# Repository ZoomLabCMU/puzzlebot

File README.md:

# PuzzleBots: Physical Coupling of Robot Swarms
Sha Yi, Zeynep Temel, Katia Sycara

Link to our [video](https://www.youtube.com/watch?v=QP3eMZXLSw4). We present a guide to make and run our PuzzleBots. A newer version is available [here](https://github.com/ZoomLabCMU/puzzlebot_v2).  

If you find our work useful, please consider citing our paper:  
```
@inproceedings{yi2021puzzlebots,
  title={PuzzleBots: Physical Coupling of Robot Swarms},
  author={Yi, Sha and Temel, Zeynep and Sycara, Katia},
  booktitle={2021 IEEE International Conference on Robotics and Automation (ICRA)},
  pages={8742--8748},
  year={2021},
  organization={IEEE}
}
```

**Software Requirement**
- python
- ROS
- Arduino

**Hardware Requirement**
- 3D Printer
- Soldering Iron
- Circuit Board Production (may use external manufacturer)
- Vicon (or other localization systems)

## Preparation
1. Assemble the robot based on instructions from the [assembly page](docs/assembly.md).
2. Burn bootloader of Arduino Pro Mini (8M, 3.3V) to the ATMega328P.
3. Configure ESP8266 WiFi module with baud rate to be 9600.

## Run the Demo
### Setup
1. Configure the system  
Change Line 83 and 105 in `code/puzzlebot_arduino/wifitcp_motor_only/wifitcp_motor_only.ino` to your own wifi and IP address.
2. Load program onto circuit board  
Open the program `code/puzzlebot_arduino/wifitcp_motor_only/wifitcp_motor_only.ino` in Arduino Studio (or other Software) and load to the circuit board built in [assembly page](docs/assembly.md).
3. Build ROS package  
Copy `code/puzzlebot_control/` into the ROS catkin source directory. Build the package.

### Run
Each robot is associated with an IP address. In our setting, robot IP address has the form `192.168.0.20[ROBOT_ID]`. The corresponding Vicon ROS topic thus has the form `vicon/p20[ROBOT_ID]/p20[ROBOT_ID]`. For example, robot #2 has an IP of `192.168.0.202`, and the corresponding vicon topic is `vicon/p202/p202`.  
This can be changed in `code/puzzlebot_control/src/puzzlebot_control/hardware_wrap.py` Line 33. To turn off the vicon callback, change Line 30 in the `hardware_wrap.py` file.

Before launching the puzzlebot node, make sure the Vicon (or other localization system) is running and publishing the corret ROS topics. Then do
```
rosrun puzzlebot_control run_hardware.py [NUMBER_OF_ROBOTS]
```
For example, with three robots, run `rosrun puzzlebot_control run_hardware.py 3`.

Then, switch on the robots by sliding the switch on the top. You are expected to see the ESP8266 LED flashes then the console will show robots are connected in sequence. The program will start once all robots are connected.

### Testing Functions
A testing function `keyboard_input_lr` is provided in `robot.py`. It can be called in `hardware_wrap.py` to send velocity command during runtime to the robots to help debug hardware issues.

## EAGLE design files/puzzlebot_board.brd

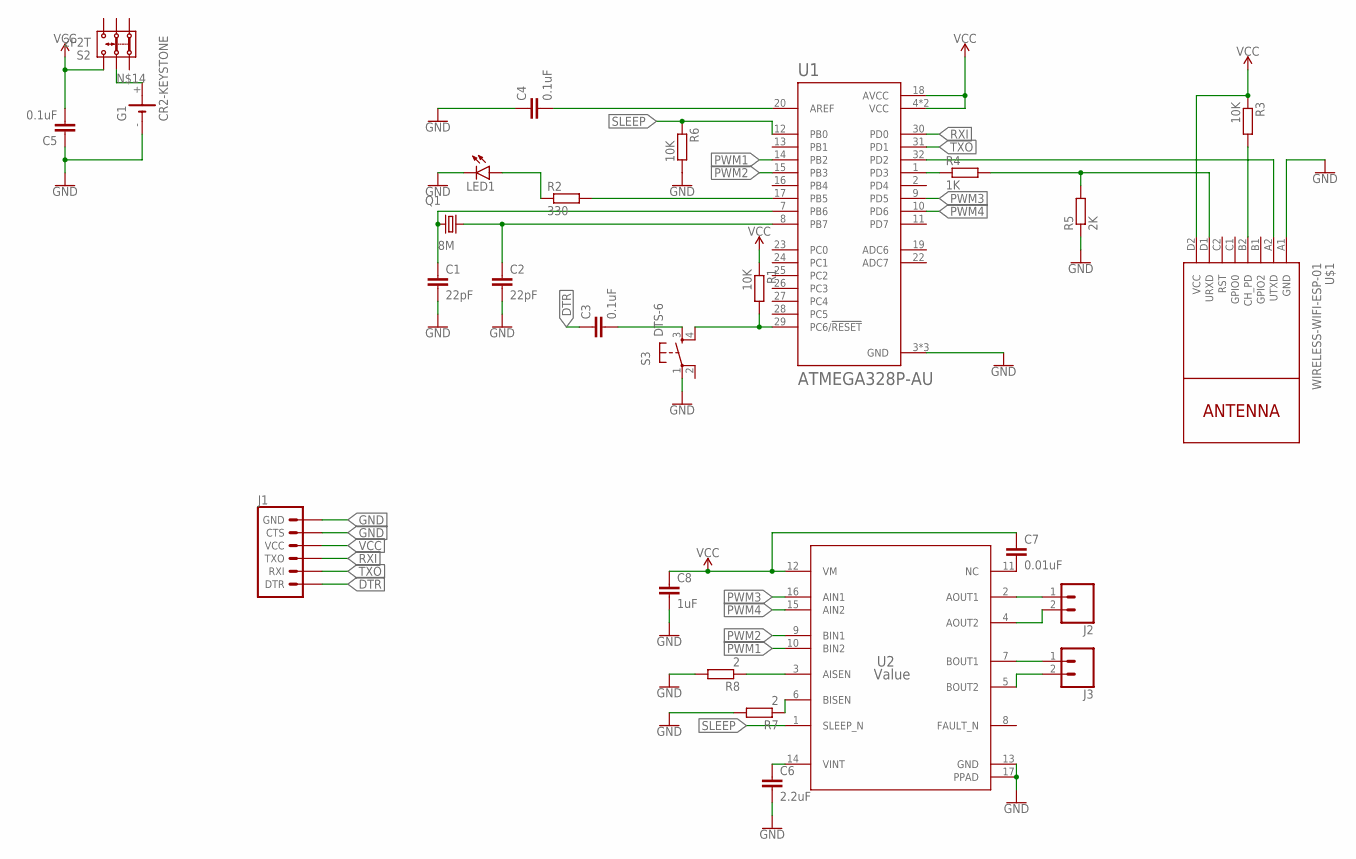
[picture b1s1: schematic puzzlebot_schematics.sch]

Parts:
C1, C2: 22pF; C0603
C3, C4, C5: 0.1uF; C0603
C6: 2.2uF; C0603
C7: 0.01uF; C0603
C8: 1uF; C0603
G1: CR2-KEYSTONE; SL-150-1/2AA/PR
J1: 6_PIN_SERIAL_TARGETLONGPADS; 1X06_LONGPADS
J2, J3: CONN_02POLAR; MOLEX-1X2
LED1: LEDCHIP-LED0805; CHIP-LED0805
Q1: 8M; CSM-7X-DU
R1, R3, R6: 10K; R0603
R2: 330; R0603
R4: 1K; R0603
R5: 2K; R0603
R7, R8: 2; R0603
S2: 2P2T
S3: DTS-6
U1: ATMEGA328P-AU; QFP80P900X900X120-32N
U2: Value; PWP0016K_M
U$1: WIRELESS-WIFI-ESP-01

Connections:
DTR: C3.1, J1.1 (DTR)
GND: C1.2, C2.2, C4.1, C5.1, C6.2, C8.2, G1.-, J1.5 (CTS), J1.6 (GND), LED1.C, R5.1, R6.2, R7.2, R8.2, S3.1, U1.3 (GND), U1.5 (GND), U1.21 (GND), U2.13 (GND), U2.17 (PPAD), U$1.A1 (GND)
unnamed: C2.1, Q1.2, U1.8 (PB7)
unnamed: C1.1, Q1.1, U1.7 (PB6)
unnamed: C3.2, S3.3
unnamed: R1.2, S3.4, U1.29 (PC6/!RESET)
unnamed: R3.2, U$1.B2 (CH_PD)
unnamed: R2.2, U1.17 (PB5)
unnamed: LED1.A, R2.1
unnamed: C4.2, U1.20 (AREF)
unnamed: U1.32 (PD2), U$1.A2 (UTXD)
unnamed: R4.1, U1.1 (PD3)
unnamed: R4.2, R5.2, U$1.D1 (URXD)
unnamed: C6.1, U2.14 (VINT)
unnamed: C7.2, U2.11 (NC)
unnamed: G1.+, S2.2.1
unnamed: R7.1, U2.6 (BISEN)
unnamed: R8.1, U2.3 (AISEN)
unnamed: J2.1, U2.2 (AOUT1)
unnamed: J3.1, U2.7 (BOUT1)
unnamed: J2.2, U2.4 (AOUT2)
unnamed: J3.2, U2.5 (BOUT2)
PWM1: U1.14 (PB2), U2.10 (BIN2)
PWM2: U1.15 (PB3), U2.9 (BIN1)
PWM3: U1.9 (PD5), U2.16 (AIN1)
PWM4: U1.10 (PD6), U2.15 (AIN2)
RXI: J1.3 (TXO), U1.30 (PD0)
SLEEP: R6.1, U1.12 (PB0), U2.1 (SLEEP_N)
TXO: J1.2 (RXI), U1.31 (PD1)
VCC: C5.2, C7.1, C8.1, J1.4 (VCC), R1.1, R3.1, S2.3.1, U1.4 (VCC), U1.6 (VCC), U1.18 (AVCC), U2.12 (VM), U$1.D2 (VCC)

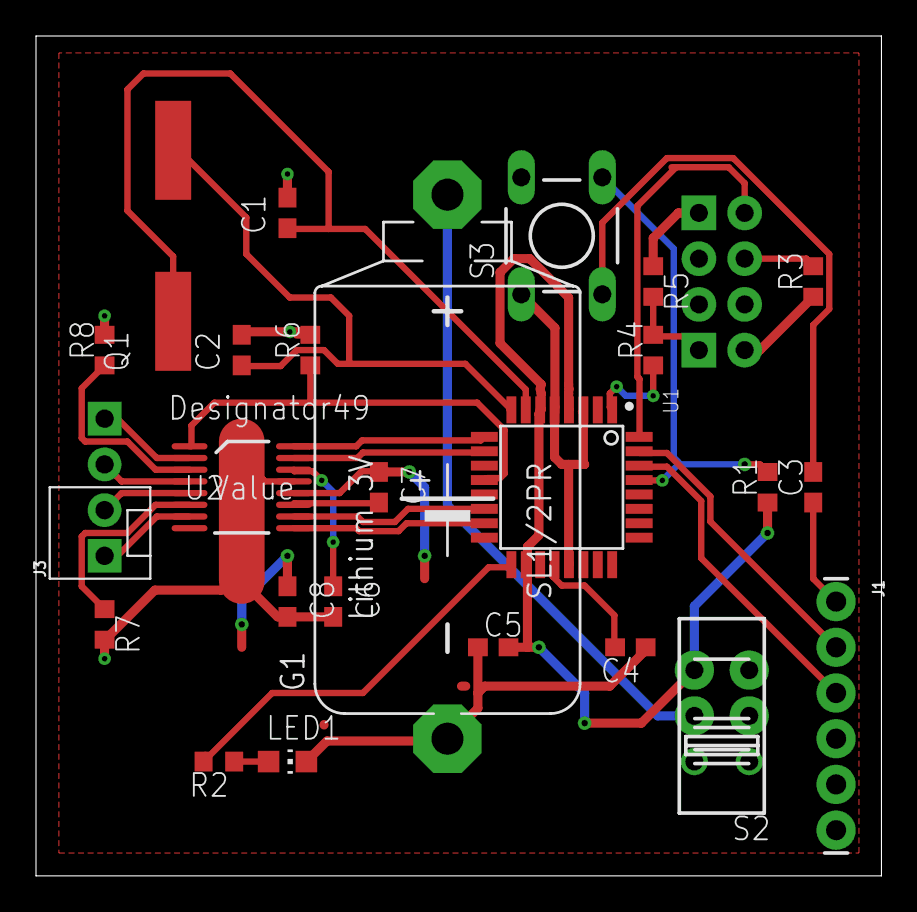
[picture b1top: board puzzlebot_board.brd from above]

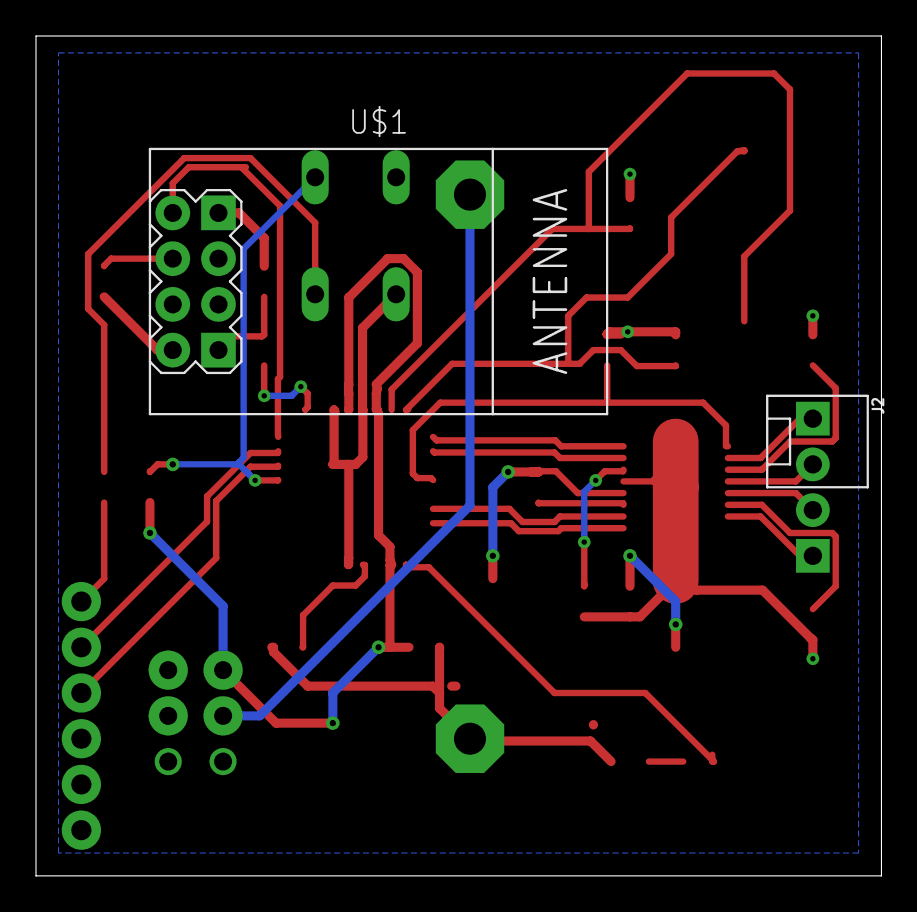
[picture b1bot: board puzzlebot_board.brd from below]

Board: 2 copper layers, 47.0 x 46.7 mm, 27 parts (2 on the bottom side), 30 nets.

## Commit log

2021-06-10 add code and update readme
2021-08-17 fix dependency
2021-08-19 handle tcp connection on ubuntu 18+
2022-02-28 update video and bibtex

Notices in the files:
parts and their libraries:
SparkFun-Connectors: Licensing: Creative Commons ShareAlike 4.0 International - https://creativecommons.org/licenses/by-sa/4.0
diy-modules: Released under the Creative Commons Attribution 4.0 International License: http://creativecommons.org/licenses/by/4.0
